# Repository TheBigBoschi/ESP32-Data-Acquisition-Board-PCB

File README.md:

# ESP32-Data-Acquisition-Board-PCB
Custom PCB holding an ESP32, various sensor, a LoRa transmitter and the power management to run off a single lithium battery, charged by solar power.

To keep the development time short for this first revision I have made extensive use of various commercial modules, such as a TP4056 module, a few TPS63020 and a CN3791 to handle the power conversion. In the second revision they will be integrated directly on the board.

Particular care has been taken to properly decouple the ESP32 power supply, as a switching regulators are slow to react to the sudden bursts of energy required by the ESP32 transmitting data, and various capacitor have been added to give time to the regulator to respond.

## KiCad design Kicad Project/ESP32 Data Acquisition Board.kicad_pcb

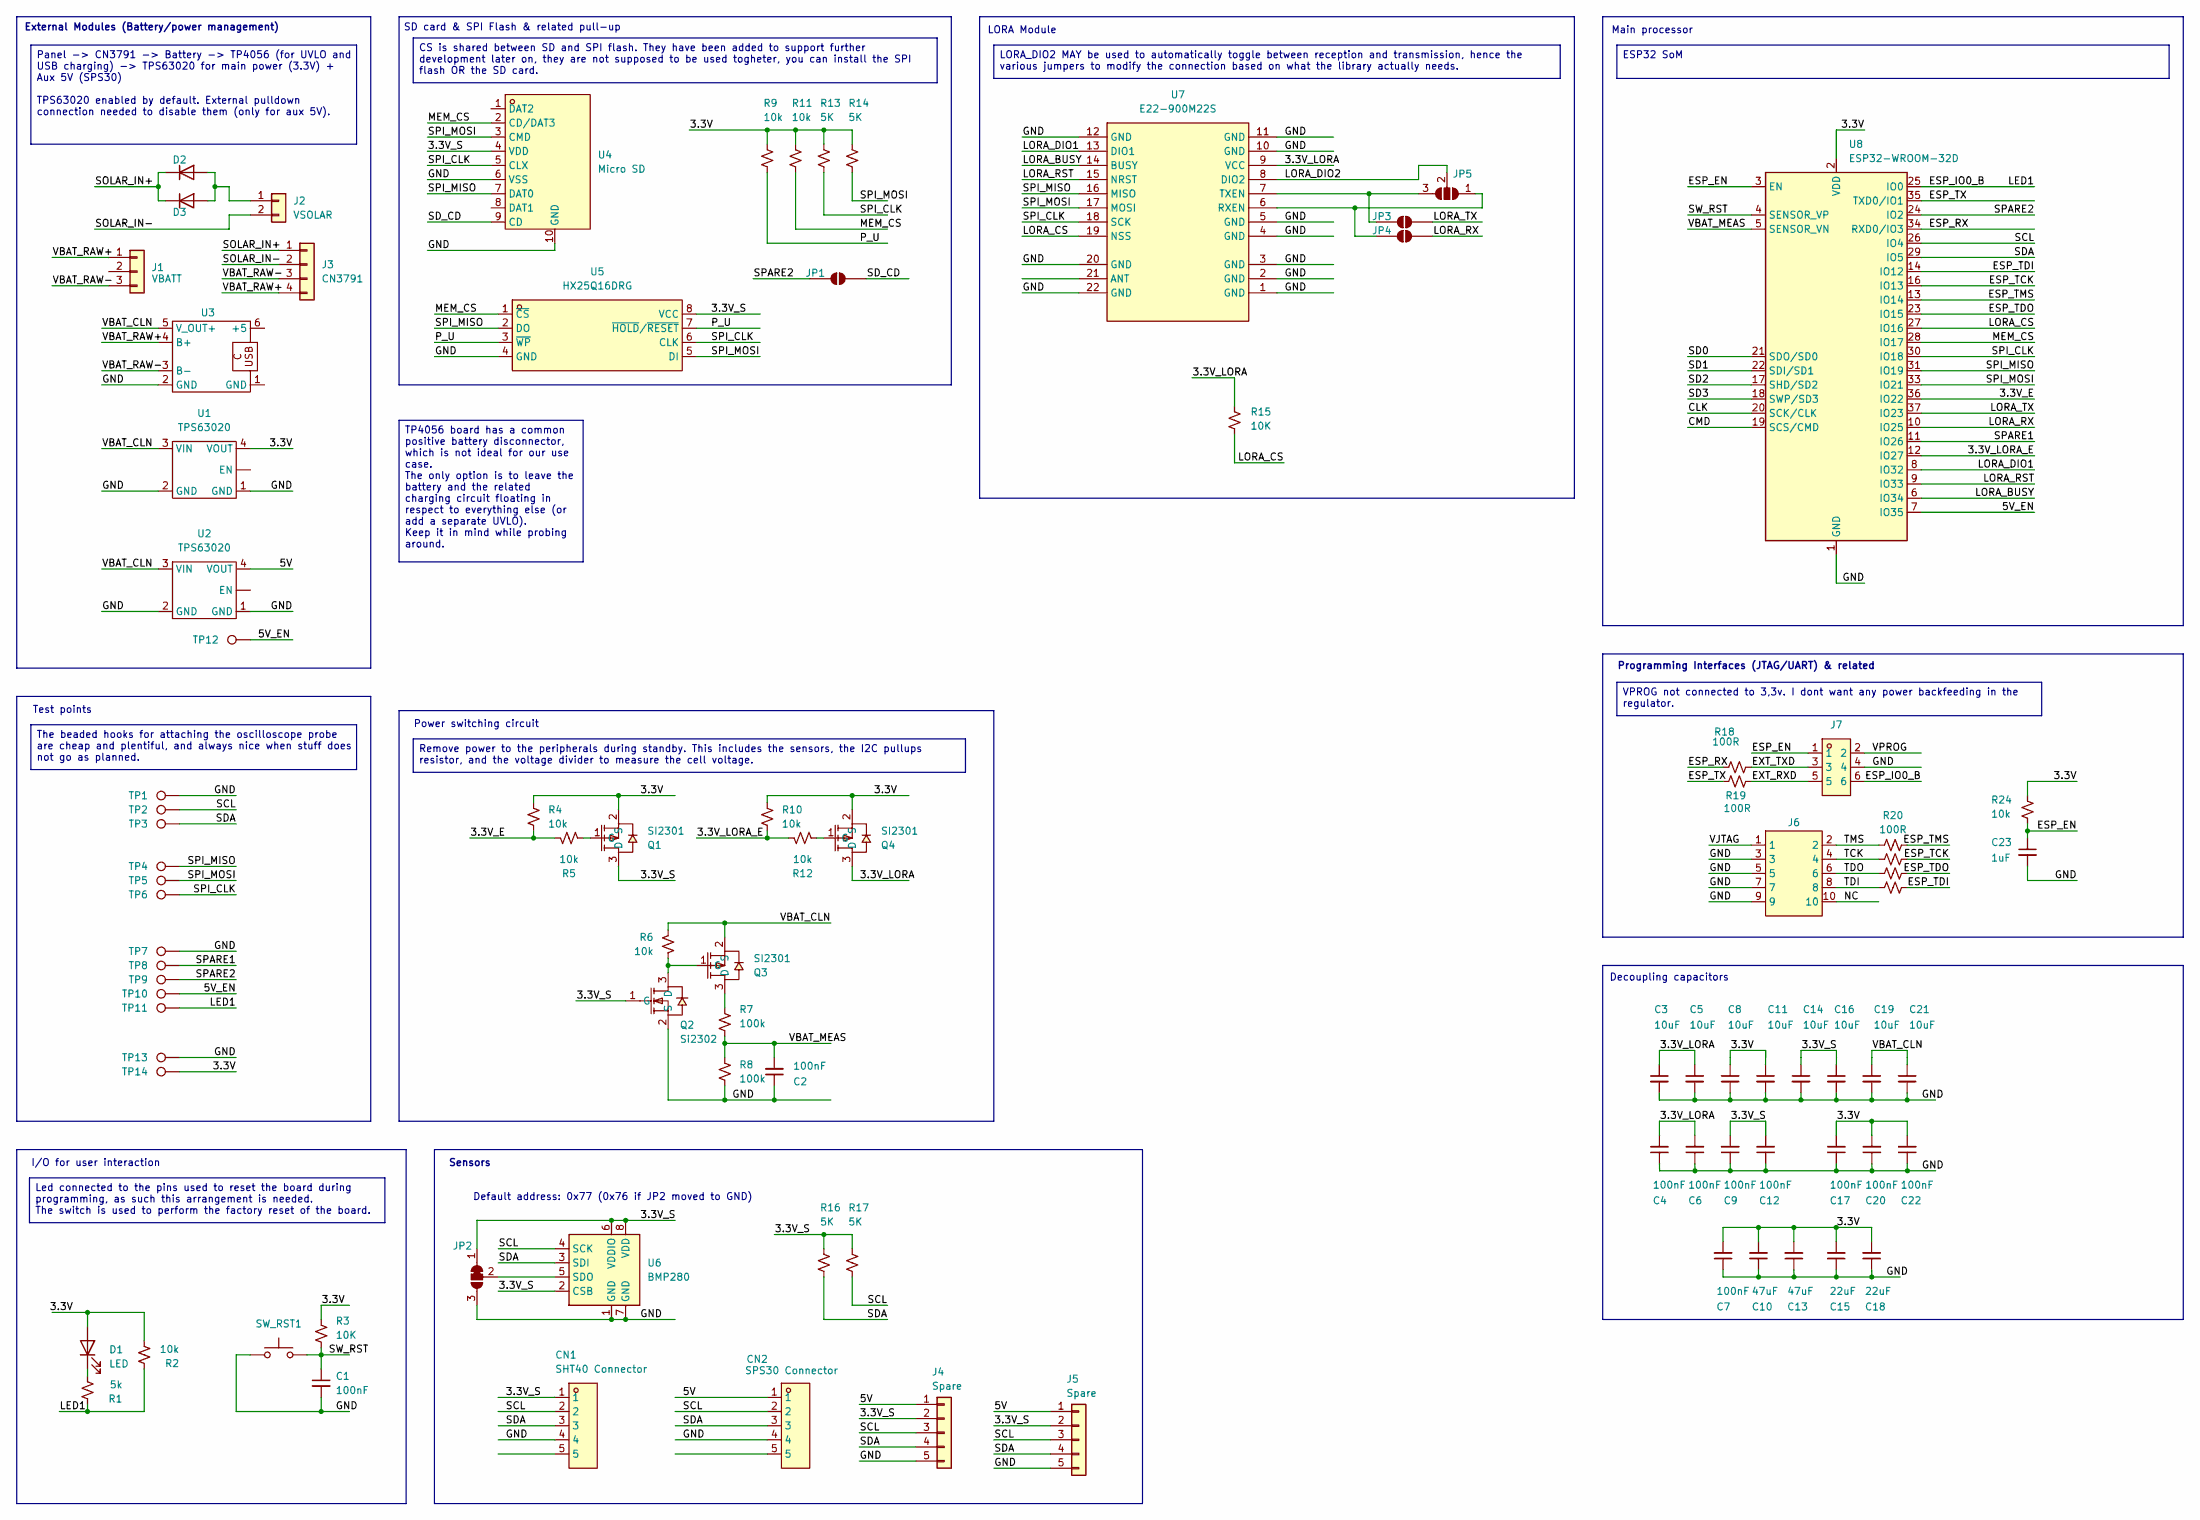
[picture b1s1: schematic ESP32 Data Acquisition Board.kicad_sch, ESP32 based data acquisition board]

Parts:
C1, C2, C4, C6, C7, C9, C12, C17, C20, C22: 100nF; C_0805_2012Metric_Pad1.18x1.45mm_HandSolder
C3, C5, C8, C11, C14, C16, C19, C21: 10uF; C_0805_2012Metric_Pad1.18x1.45mm_HandSolder
C10, C13: 47uF; C_1206_3216Metric_Pad1.33x1.80mm_HandSolder
C15, C18: 22uF; C_0805_2012Metric_Pad1.18x1.45mm_HandSolder
C23: 1uF; C_0805_2012Metric_Pad1.18x1.45mm_HandSolder
CN1: SHT40 Connector; CONN-TH_5P-P2.54_KF141R-2.54-5P; MPN KF141R-2.54-5P; LCSC Part C475127
CN2: SPS30 Connector; CONN-TH_5P-P2.54_KF141R-2.54-5P; MPN KF141R-2.54-5P; LCSC Part C475127
D1: LED; LED_0805_2012Metric_Pad1.15x1.40mm_HandSolder
D2, D3: M7F; D_SMA_Handsoldering
J1: VBATT; PinHeader_1x03_P2.54mm_Vertical
J2: VSOLAR; PinHeader_1x02_P2.54mm_Vertical
J3: CN3791; PinHeader_1x04_P2.54mm_Vertical
J4, J5: Spare; PinSocket_1x05_P2.54mm_Vertical
J6: HDR-IDC-2.54-2X5P; IDC-TH_10P-P2.54_C5665; MPN 2.54-2*5P简牛; LCSC Part C5665
J7: BH254V-6P; IDC-TH_6P-P2.54-V-R2-C3-S2.54; MPN BH254V-6P; LCSC Part C492441
JP1, JP3, JP4: SolderJumper_2_Open; SolderJumper-2_P1.3mm_Open_RoundedPad1.0x1.5mm
JP2: SolderJumper_3_Bridged12; SolderJumper-3_P1.3mm_Bridged12_RoundedPad1.0x1.5mm
JP5: SolderJumper_3_Open; SolderJumper-3_P1.3mm_Open_RoundedPad1.0x1.5mm_NumberLabels
Q1, Q3, Q4: SI2301; SOT-23-3_L3.0-W1.7-P0.95-LS2.9-BR; MPN SI2301CDS-T1-GE3; LCSC Part C10487
Q2: Si2302; SOT-23_L2.9-W1.3-P1.90-LS2.4-BR; MPN Si2302CDS-T1-GE3; LCSC Part C10488
R1: 5k; R_0805_2012Metric_Pad1.20x1.40mm_HandSolder
R2, R4, R5, R6, R9, R10, R11, R12, R24: 10k; R_0805_2012Metric_Pad1.20x1.40mm_HandSolder
R3, R15: 10K; R_0805_2012Metric_Pad1.20x1.40mm_HandSolder
R7, R8: 100k; R_0805_2012Metric_Pad1.20x1.40mm_HandSolder
R13, R14, R16, R17: 5K; R_0805_2012Metric_Pad1.20x1.40mm_HandSolder
R18, R19, R20, R21, R22, R23: 100R; R_0805_2012Metric_Pad1.20x1.40mm_HandSolder
SW_RST1: SW-SMD_4P-L4.5-W4.5-P3.00-LS6.6; MPN TS110926045; LCSC Part C22375351
TP1, TP2, TP3, TP4, TP5, TP6, TP7, TP8, TP9, TP10, TP11: TestPoint; TestPoint_Loop_D3.50mm_Drill1.4mm_Beaded
TP12: TestPoint; TestPoint_THTPad_D2.0mm_Drill1.0mm
TP13, TP14: TestPoint; TestPoint_Pad_1.5x1.5mm
U1, U2: TPS63020
U3: TP4056 BOARD
U4: Micro SD; SIM-SMD_LX_XDFP-0090-012; MPN TF-CARD-9P; LCSC Part C53144700
U5: HX25Q16DRG; SOP-8_L4.9-W3.9-P1.27-LS6.0-BL; MPN HX25Q16DRG; LCSC Part C22439610
U6: BMP280; Bosch_LGA-8_2x2.5mm_P0.65mm_ClockwisePinNumbering
U7: E22-900M22S; WIRELM-SMD_E22-900M22S; MPN E22-900M22S; LCSC Part C411293
U8: ESP32-WROOM-32D

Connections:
/3.3V: C7.2, C8.1, C10.2, C11.1, C13.2, C15.2, C17.2, C18.2, C20.2, C22.2, D1.2 (A), Q1.2 (S), Q4.2 (S), R2.1, R3.2, R4.2, R9.2, R10.2, R11.2, R13.2, R14.2, R24.2, TP14.1 (1_1), U1.4 (VOUT), U8.2 (VDD)
/3.3V_E: R4.1, R5.1, U8.36 (IO22)
/3.3V_LORA: C3.1, C4.2, C5.1, C6.2, Q4.3 (D), R15.2, U7.9 (VCC)
/3.3V_LORA_E: R10.1, R12.1, U8.12 (IO27)
/3.3V_S: C9.2, C12.2, C14.1, C16.1, CN1.1, J4.2, J5.2, JP2.1 (A), Q1.3 (D), Q2.1 (G), R16.2, R17.2, U4.4 (VDD), U5.8 (VCC), U6.2 (CSB), U6.6 (VDDIO), U6.8 (VDD)
/5V: CN2.1, J4.1, J5.1, U2.4 (VOUT)
/5V_EN: TP10.1 (1_1), TP12.1 (1_1), U8.7 (IO35)
/CLK: U8.20 (SCK/CLK)
/CMD: U8.19 (SCS/CMD)
/ESP_EN: C23.1, J7.1, R24.1, U8.3 (EN)
/ESP_IO0_B: J7.6, R1.2, R2.2, TP11.1 (1_1), U8.25 (IO0)
/ESP_RX: R18.1, U8.34 (RXD0/IO3)
/ESP_TCK: R21.2, U8.16 (IO13)
/ESP_TDI: R23.2, U8.14 (IO12)
/ESP_TDO: R22.2, U8.23 (IO15)
/ESP_TMS: R20.2, U8.13 (IO14)
/ESP_TX: R19.1, U8.35 (TXD0/IO1)
/EXT_RXD: J7.5, R19.2
/EXT_TXD: J7.3, R18.2
/GND: C1.2, C2.1, C3.2, C4.1, C5.2, C6.1, C7.1, C8.2, C9.1, C10.1, C11.2, C12.1, C13.1, C14.2, C15.1, C16.2, C17.1, C18.1, C19.2, C20.1, C21.2, C22.1, C23.2, CN1.4, CN2.4, J4.5, J5.5, J6.3, J6.5, J6.7, J6.9, J7.4, JP2.3 (B), Q2.2 (S), R8.1, SW_RST1.1, TP1.1 (1_1), TP7.1 (1_1), TP13.1 (1_1), U1.1 (GND), U1.2 (GND), U2.1 (GND), U2.2 (GND), U3.2 (GND), U4.6 (VSS), U4.10 (GND), U5.4 (GND), U6.1 (GND), U6.7 (GND), U7.1 (GND), U7.2 (GND), U7.3 (GND), U7.4 (GND), U7.5 (GND), U7.10 (GND), U7.11 (GND), U7.12 (GND), U7.20 (GND), U7.22 (GND), U8.1 (GND), U8.15 (GND), U8.38 (GND), U8.39 (GND)
/LORA_BUSY: U7.14 (BUSY), U8.6 (IO34)
/LORA_CS: R15.1, U7.19 (NSS), U8.27 (IO16)
/LORA_DIO1: U7.13 (DIO1), U8.8 (IO32)
/LORA_DIO2: JP5.2 (C), U7.8 (DIO2)
/LORA_RST: U7.15 (NRST), U8.9 (IO33)
/LORA_RX: JP4.2 (B), U8.10 (IO25)
/LORA_TX: JP3.2 (B), U8.37 (IO23)
/MEM_CS: R11.1, U4.2 (CD/DAT3), U5.1 (~CS), U8.28 (IO17)
/NC: J6.10
/P_U: R9.1, U5.3 (~WP), U5.7 (~HOLD/~RESET)
/SCL: CN1.2, CN2.2, J4.3, J5.3, R17.1, TP2.1 (1_1), U6.4 (SCK), U8.26 (IO4)
/SD0: U8.21 (SDO/SD0)
/SD1: U8.22 (SDI/SD1)
/SD2: U8.17 (SHD/SD2)
/SD3: U8.18 (SWP/SD3)
/SDA: CN1.3, CN2.3, J4.4, J5.4, R16.1, TP3.1 (1_1), U6.3 (SDI), U8.29 (IO5)
/SD_CD: JP1.2 (B), U4.9 (CD)
/SOLAR_IN+: D2.1 (K), D3.1 (K), J3.1
/SOLAR_IN-: J2.2, J3.2
/SPARE1: TP8.1 (1_1), U8.11 (IO26)
/SPARE2: JP1.1 (A), TP9.1 (1_1), U8.24 (IO2)
/SPI_CLK: R13.1, TP6.1 (1_1), U4.5 (CLX), U5.6 (CLK), U7.18 (SCK), U8.30 (IO18)
/SPI_MISO: TP4.1 (1_1), U4.7 (DAT0), U5.2 (DO), U7.16 (MISO), U8.31 (IO19)
/SPI_MOSI: R14.1, TP5.1 (1_1), U4.3 (CMD), U5.5 (DI), U7.17 (MOSI), U8.33 (IO21)
/SW_RST: C1.1, R3.1, SW_RST1.2, U8.4 (SENSOR_VP)
/TCK: J6.4, R21.1
/TDI: J6.8, R23.1
/TDO: J6.6, R22.1
/TMS: J6.2, R20.1
/VBAT_CLN: C19.1, C21.1, Q3.2 (S), R6.2, U1.3 (VIN), U2.3 (VIN), U3.5 (V_OUT+)
/VBAT_MEAS: C2.2, R7.1, R8.2, U8.5 (SENSOR_VN)
/VBAT_RAW+: J1.1, J3.4, U3.4 (B+)
/VBAT_RAW-: J1.3, J3.3, U3.3 (B-)
/VJTAG: J6.1
/VPROG: J7.2
unnamed: D1.1 (K), R1.1
unnamed: D2.2 (A), D3.2 (A), J2.1
unnamed: JP2.2 (C), U6.5 (SDO)
unnamed: JP3.1 (A), JP5.3 (B), U7.7 (TXEN)
unnamed: JP4.1 (A), JP5.1 (A), U7.6 (RXEN)
unnamed: Q1.1 (G), R5.2
unnamed: Q2.3 (D), Q3.1 (G), R6.1
unnamed: Q3.3 (D), R7.2
unnamed: Q4.1 (G), R12.2

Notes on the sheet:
Main processor
Test points
SD card & SPI Flash & related pull-up
Power switching circuit
LORA Module
External Modules (Battery/power management)
Decoupling capacitors
Default address: 0x77 (0x76 if JP2 moved to GND)
Sensors
Programming Interfaces (JTAG/UART) & related
I/O for user interaction
ESP32 SoM
LORA_DIO2 MAY be used to automatically toggle between reception and transmission, hence the various jumpers to modify the connection based on what the library actually needs.
Panel -> CN3791 -> Battery -> TP4056 (for UVLO and USB charging) -> TPS63020 for main power (3.3V) + Aux 5V (SPS30) TPS63020 enabled by default. External pulldown connection needed to disable them (only for aux 5V).
The beaded hooks for attaching the oscilloscope probe are cheap and plentiful, and always nice when stuff does not go as planned.
VPROG not connected to 3,3v. I dont want any power backfeeding in the regulator.
CS is shared between SD and SPI flash. They have been added to support further development later on, they are not supposed to be used togheter, you can install the SPI flash OR the SD card.
Led connected to the pins used to reset the board during programming, as such this arrangement is needed. The switch is used to perform the factory reset of the board.
TP4056 board has a common positive battery disconnector, which is not ideal for our use case. The only option is to leave the battery and the related charging circuit floating in respect to everything else (or add a separate UVLO). Keep it in mind while probing around.
Remove power to the peripherals during standby. This includes the sensors, the I2C pullups resistor, and the voltage divider to measure the cell voltage.

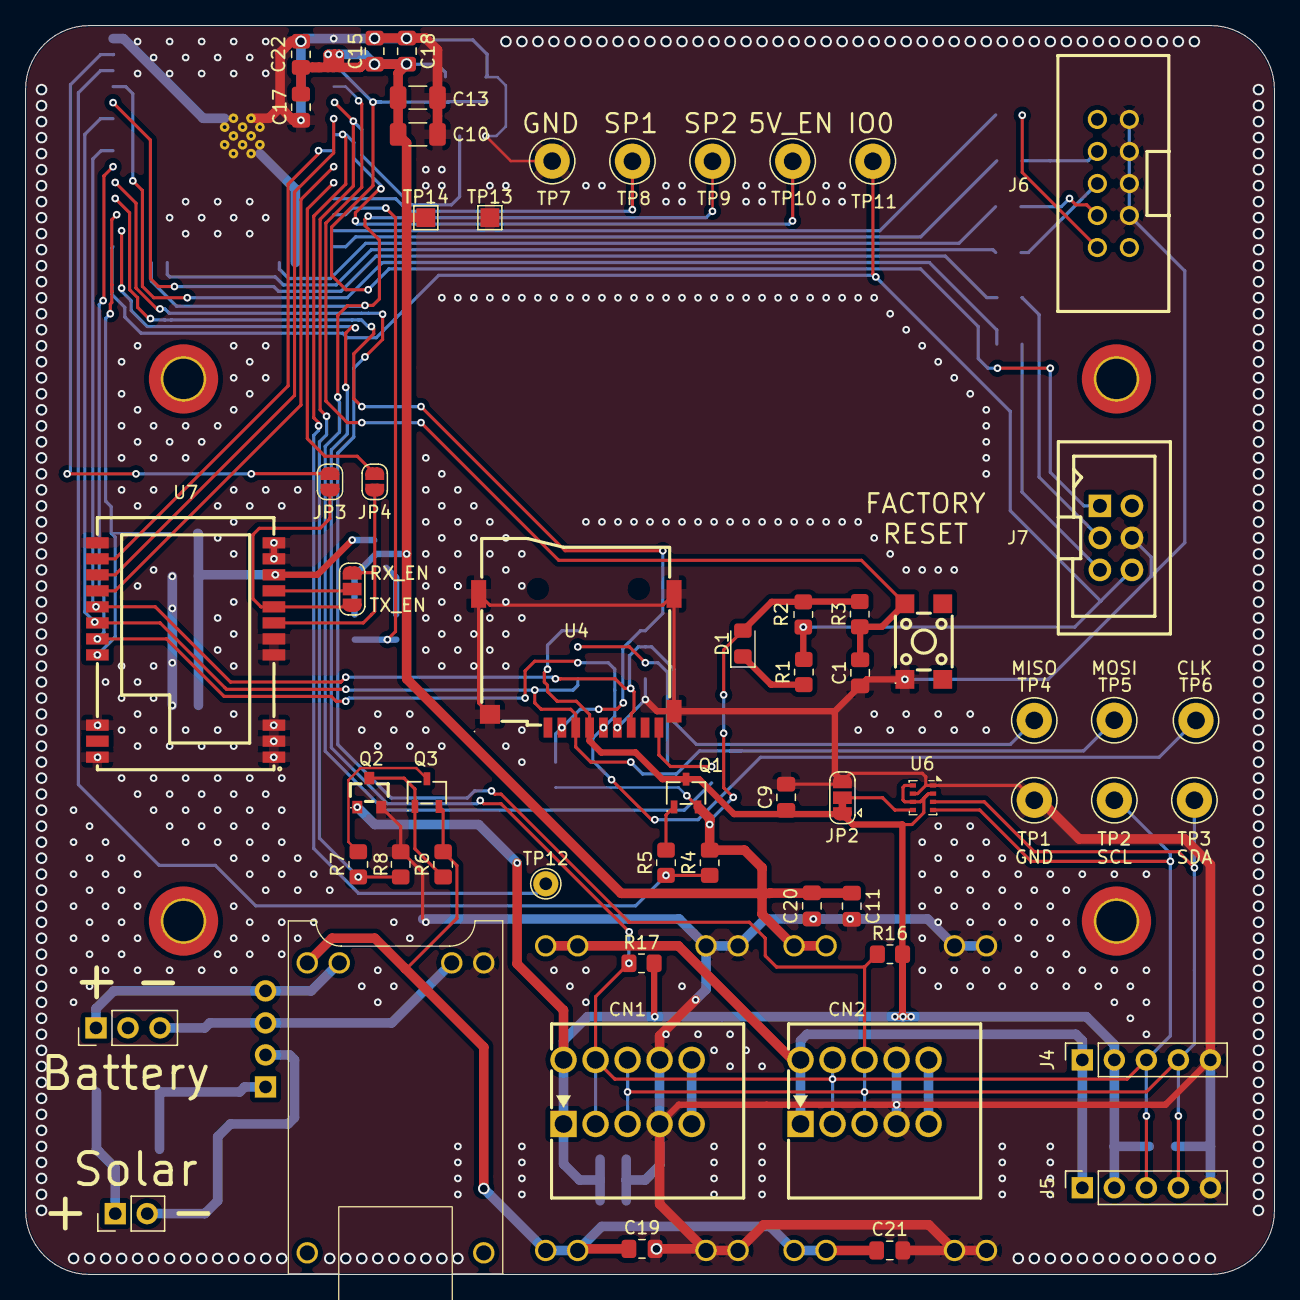
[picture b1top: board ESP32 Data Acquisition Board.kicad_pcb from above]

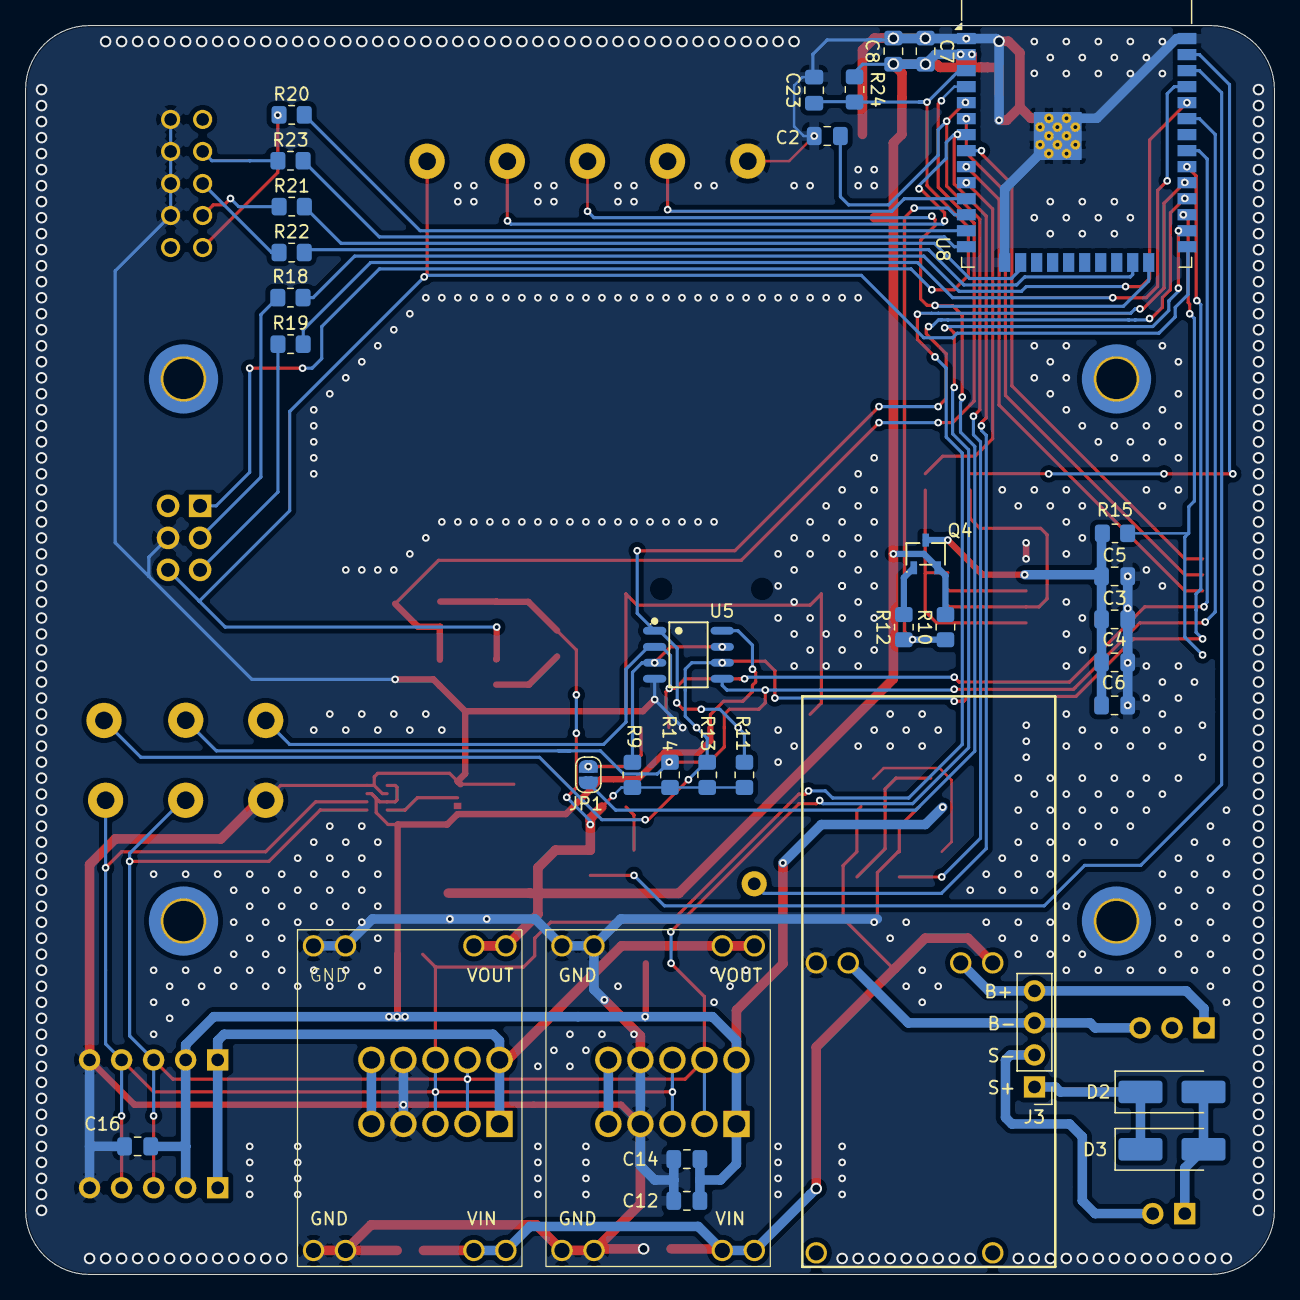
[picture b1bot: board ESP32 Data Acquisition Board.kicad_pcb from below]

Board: 2 copper layers, 99.1 x 99.1 mm, 91 parts (34 on the bottom side), 55 nets.

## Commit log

2026-06-07 Update README with project details and power management info
    Expanded the project description with details on development choices and power supply considerations.
2026-06-07 Updated readme, included interactive BoM, added 3D renders and schematics.
